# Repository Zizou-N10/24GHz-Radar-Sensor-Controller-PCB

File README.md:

# 24 GHz Radar Sensor Controller PCB

A custom-designed, 2-layer radar sensor controller PCB developed using KiCad, featuring an ESP32-C3 microcontroller and an expansion interface for 24 GHz FMCW radar modules.
|

This project was an opportunity to explore electronic design automation (EDA), schematic design, PCB layout, component selection, and manufacturing preparation.

## Project Overview

The board is designed to act as a controller and interface for a 24 GHz radar sensor module. It uses an ESP32-C3 microcontroller and includes power regulation, status indicators, user-control buttons, and an expansion header.

The design was developed in KiCad, from schematic capture to PCB routing and manufacturing-file generation.

## Project Gallery

### 3D PCB Renders

### PCB Layout

### Schematic

### Bill of Materials

### Manufacturing Verification

## Technical Specifications

| Feature | Description |

|---|---|

| Microcontroller | ESP32-C3 |

| Architecture | 32-bit RISC-V |

| Radar Interface | Expansion header for compatible 24 GHz FMCW radar modules |

| Example Radar Module | Hi-Link HLK-LD2410 |

| Power Input | USB Type-C, 5V |

| Operating Voltage | 3.3V regulated |

| PCB Layers | 2 |

| Design Software | KiCad |

| PCB Manufacturer Verification | JLCPCB |

## Key Features

- USB Type-C power input.

- 5V to 3.3V voltage regulation.

- ESP32-C3 microcontroller.

- Status and target-detection LED indicators.

- Reset and boot buttons.

- Expansion header for compatible radar modules.

- Two-layer PCB design.

## Design and Engineering

The project involved several stages of electronic hardware development:

### 1. Schematic Design

- Component selection and placement.

- Power distribution design.

- Microcontroller connections.

- Peripheral and expansion-header connections.

### 2. PCB Layout

- Component placement and board organisation.

- Signal routing across two copper layers.

- Ground-plane and power-distribution considerations.

- Design-rule checking (DRC).

### 3. Manufacturing Preparation

- Gerber file generation.

- Bill of Materials (BOM) export.

- Fabrication-file verification through JLCPCB.

## Design Verification

The completed KiCad design achieved:

- 0 DRC errors.

- 0 DRC warnings.

- 0 unconnected items.

The exported Gerber files were also submitted to JLCPCB's automated verification system.

These results indicate that the design passed the checks performed at this stage. Physical fabrication, assembly, electrical testing, and radar-module integration have not yet been completed.

## Repository Structure

```text

24GHz-Radar-Sensor-Controller-PCB/

│

├── Hardware/

│   ├── KiCad_Project/

│   │   ├── radar-controller.kicad_pcb

│   │   ├── radar-controller.kicad_pro

│   │   └── radar-controller.kicad_sch

│   │

│   ├── Schematics/

│   ├── PCB_Layout/

│   └── 3D_Models/

│

├── Manufacturing/

│   ├── Gerber_Files/

│   ├── BOM/

│   │   └── radar-controller.csv

│   └── Drill_Files/

│

├── Documentation/

│

├── Images/

│   ├── 3D View 1.png

│   ├── 3D View 2.png

│   ├── PCB.png

│   ├── Schematic.png

│   ├── BOM.png

│   └── JLCPCB.png

│

└── README.md

```

## Future Improvements

The next stages of development include:

- Physically fabricating and assembling the PCB.

- Testing the 5V input and 3.3V power regulation.

- Verifying ESP32-C3 operation.

- Integrating a compatible 24 GHz radar module.

- Developing firmware for radar data acquisition and processing.

- Testing the complete system under real operating conditions.

## Learning Experience

This was my first PCB design project, and I began with only a basic understanding of electrical and electronic concepts.

Throughout the process, I explored schematic capture, component selection, PCB routing, design-rule checking, and manufacturing preparation.

I also used Google Gemini as an interactive learning assistant to understand unfamiliar concepts and troubleshoot design decisions. The schematic design and PCB routing were carried out by me.

The project helped me develop a practical understanding of how electronic hardware moves from an initial concept to a manufacturable PCB design.

## Tools and Technologies

- **KiCad** — Electronic design automation and PCB layout.

- **ESP32-C3** — Microcontroller.

- **USB Type-C** — Power input.

- **24 GHz FMCW Radar** — Intended sensor interface.

- **JLCPCB** — Manufacturing-file verification.

- **Google Gemini** — Interactive learning assistance.

---

*This repository documents the design and manufacturing preparation stages. Physical hardware validation is still pending.*

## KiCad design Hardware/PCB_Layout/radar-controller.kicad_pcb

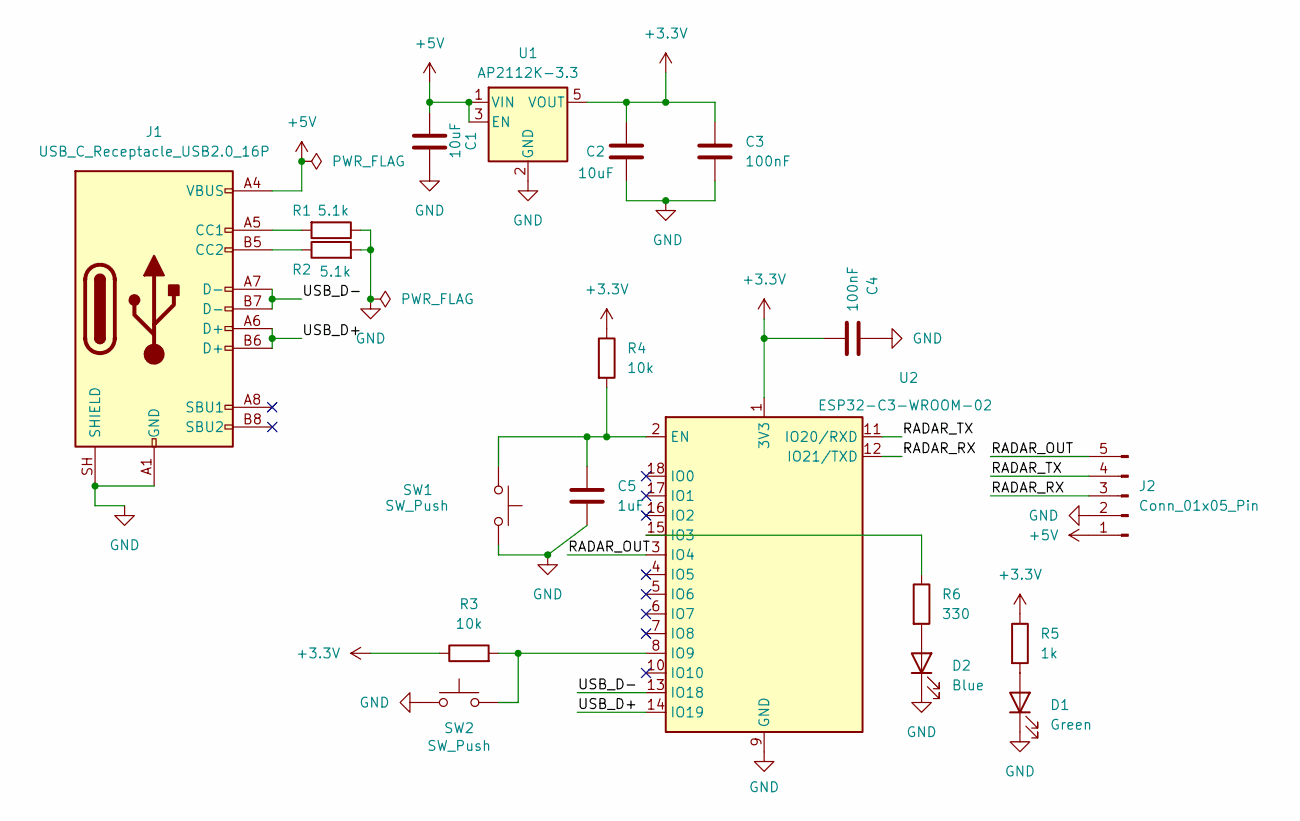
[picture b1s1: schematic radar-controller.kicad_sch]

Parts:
C1, C2: 10uF; C_0805_2012Metric
C3, C4: 100nF; C_0805_2012Metric
C5: 1uF; C_0805_2012Metric
D1: Green; LED_0805_2012Metric
D2: Blue; LED_0805_2012Metric
J1: USB_C_Receptacle_USB2.0_16P; USB_C_Receptacle_HRO_TYPE-C-31-M-12
J2: Conn_01x05_Pin; PinHeader_1x05_P2.54mm_Vertical
R1, R2: 5.1k; R_0805_2012Metric
R3, R4: 10k; R_0805_2012Metric
R5: 1k; R_0805_2012Metric
R6: 330; R_0805_2012Metric
SW1, SW2: SW_Push; SW_Push_SPST_NO_Alps_SKRK
U1: AP2112K-3.3; SOT-23-5
U2: ESP32-C3-WROOM-02

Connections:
+3.3V: C2.1, C3.2, C4.2, R3.1, R4.1, R5.1, U1.5 (VOUT), U2.1 (3V3)
+5V: C1.1, J1.A4 (VBUS), J1.A9 (VBUS), J1.B4 (VBUS), J1.B9 (VBUS), J2.1, U1.1 (VIN), U1.3 (EN)
/RADAR_OUT: J2.5, U2.3 (IO4)
/RADAR_RX: J2.3, U2.12 (IO21/TXD)
/RADAR_TX: J2.4, U2.11 (IO20/RXD)
/USB_D+: J1.A6 (D+), J1.B6 (D+), U2.14 (IO19)
/USB_D-: J1.A7 (D-), J1.B7 (D-), U2.13 (IO18)
GND: C1.2, C2.2, C3.1, C4.1, C5.2, D1.1 (K), D2.1 (K), J1.A1 (GND), J1.A12 (GND), J1.B1 (GND), J1.B12 (GND), J1.SH (SHIELD), J2.2, R1.1, R2.2, SW1.2, SW2.1, U1.2 (GND), U2.9 (GND), U2.19 (GND)
unnamed: D1.2 (A), R5.2
unnamed: D2.2 (A), R6.2
unnamed: J1.A5 (CC1), R1.2
unnamed: J1.B5 (CC2), R2.1
unnamed: C5.1, R4.2, SW1.1, U2.2 (EN)
unnamed: R6.1, U2.15 (IO3)
unnamed: R3.2, SW2.2, U2.8 (IO9)

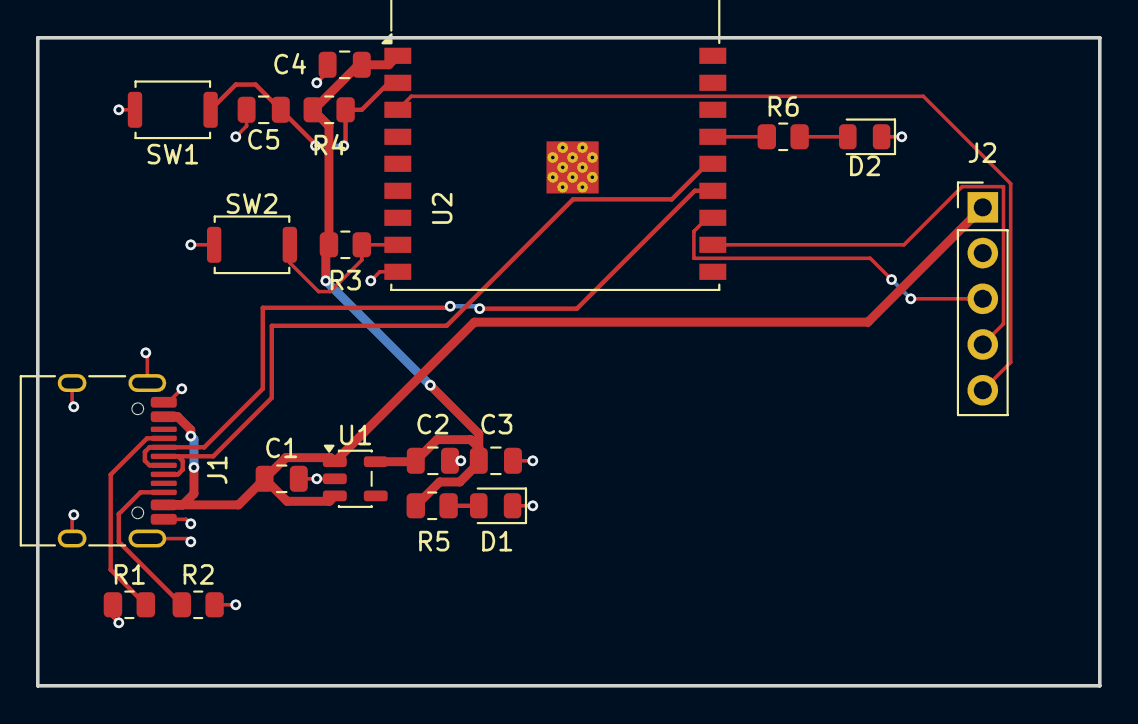
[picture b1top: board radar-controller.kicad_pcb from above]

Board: 2 copper layers, 59.0 x 36.0 mm, 19 parts (0 on the bottom side), 15 nets.
